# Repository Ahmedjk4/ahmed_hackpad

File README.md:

# A Simple Macropad built for hackpad stardance mission

it includes 4 switches, a rotary encoder

## Dimensions

PCB Dimensions: 82.5mm x 69.5mm
Case Dimensions: 102.9 mm x 89.9 mm

## BOM

- 4 Cherry MX Switches
- 1 Rotary Encoder With Switch
- Seeduino XIAO Rasperry PI Pico (RP2040)

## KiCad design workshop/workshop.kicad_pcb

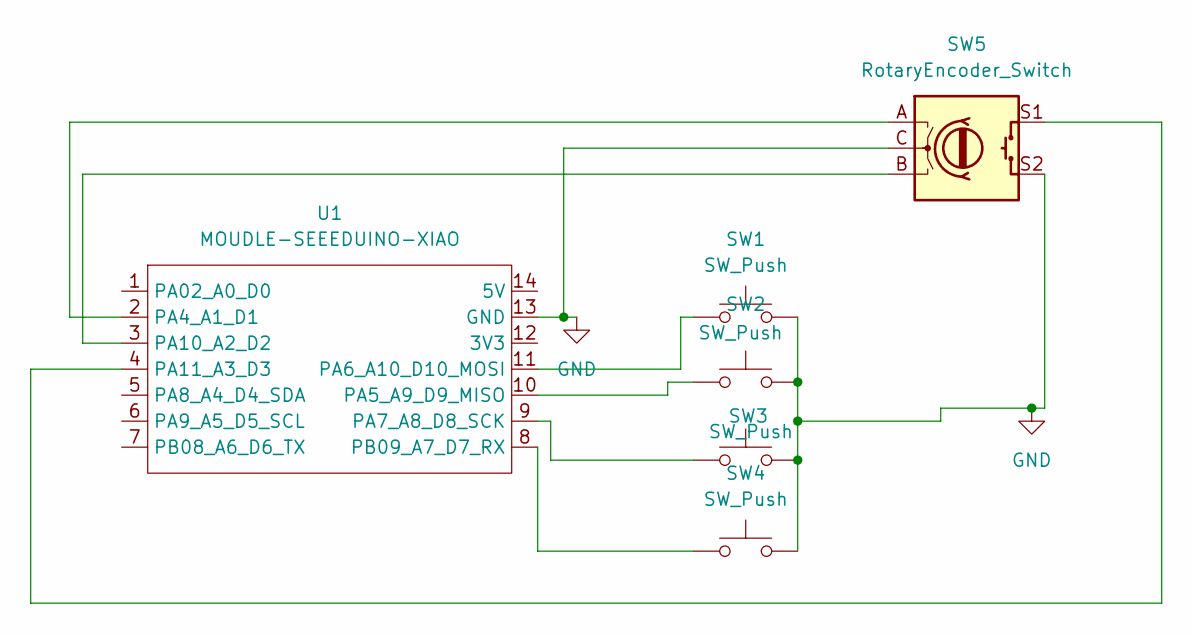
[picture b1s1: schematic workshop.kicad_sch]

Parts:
SW1, SW2, SW3, SW4: SW_Push; SW_Cherry_MX_1.00u_PCB
SW5: RotaryEncoder_Switch; RotaryEncoder_Alps_EC11E-Switch_Vertical_H20mm
U1: MOUDLE-SEEEDUINO-XIAO; XIAO-Generic-Hybrid-14P-2.54-21X17.8MM

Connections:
GND: SW1.2, SW2.2, SW3.2, SW4.2, SW5.C, SW5.S2, U1.13 (GND)
unnamed: SW5.A, U1.2 (PA4_A1_D1)
unnamed: SW2.1, U1.10 (PA5_A9_D9_MISO)
unnamed: SW1.1, U1.11 (PA6_A10_D10_MOSI)
unnamed: SW3.1, U1.9 (PA7_A8_D8_SCK)
unnamed: SW5.B, U1.3 (PA10_A2_D2)
unnamed: SW5.S1, U1.4 (PA11_A3_D3)
unnamed: SW4.1, U1.8 (PB09_A7_D7_RX)

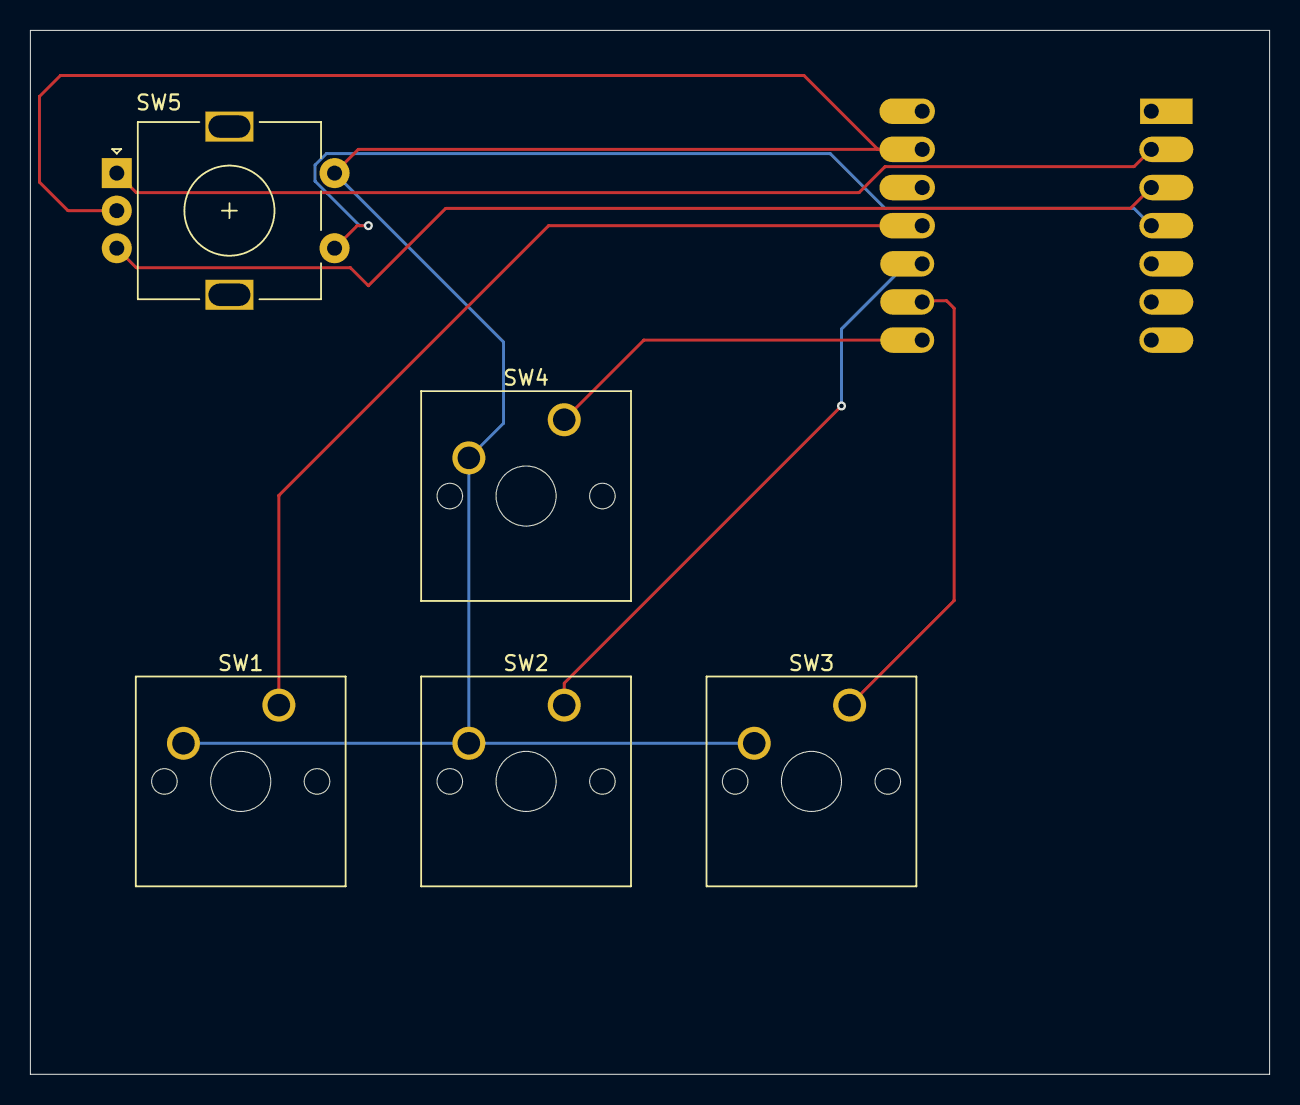
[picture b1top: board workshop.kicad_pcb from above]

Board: 2 copper layers, 82.5 x 69.5 mm, 6 parts (1 on the bottom side), 8 nets.
